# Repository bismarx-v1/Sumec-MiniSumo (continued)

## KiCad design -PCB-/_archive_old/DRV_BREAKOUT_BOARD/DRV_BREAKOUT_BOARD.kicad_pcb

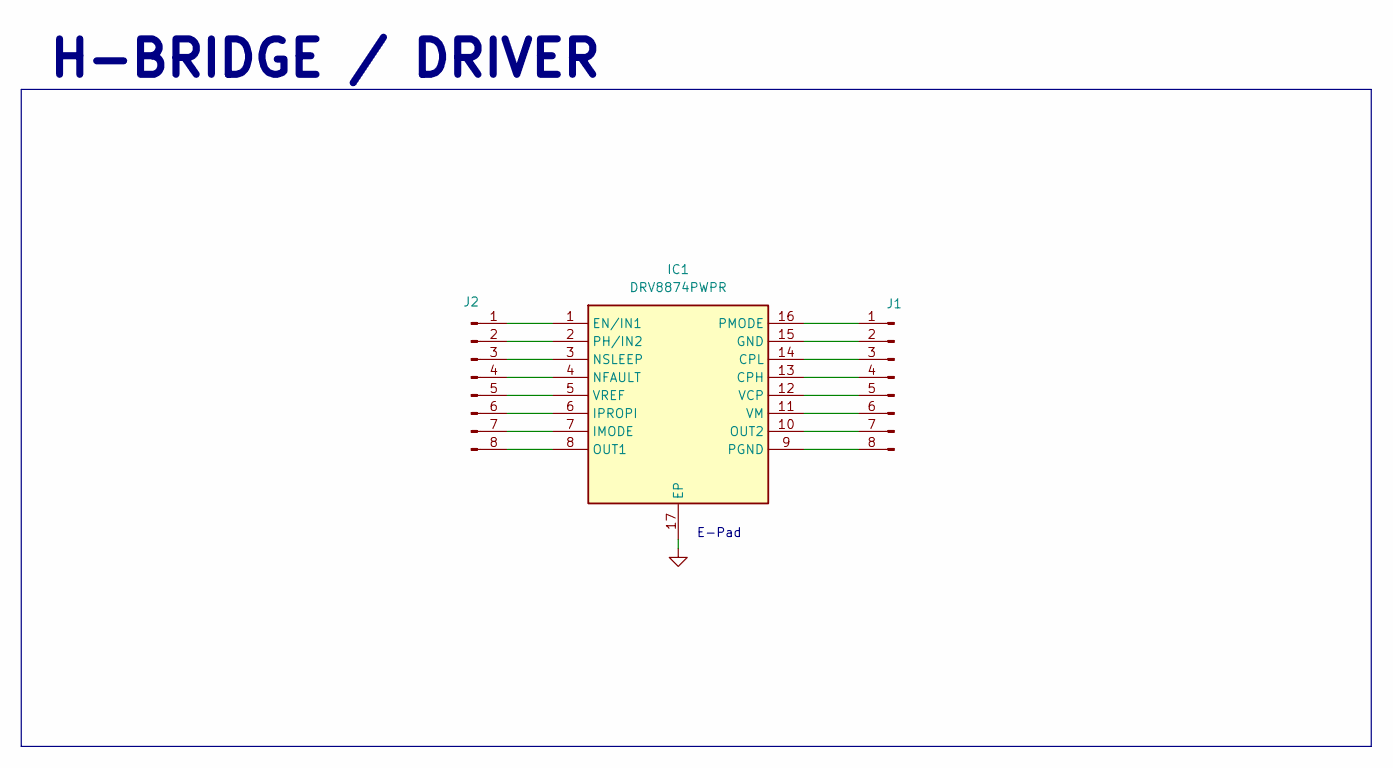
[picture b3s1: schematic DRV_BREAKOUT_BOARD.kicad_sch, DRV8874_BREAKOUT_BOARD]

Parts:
IC1: DRV8874PWPR; DRV8874; Manufacturer_Part_Number DRV8874PWPR; Mouser Part Number 595-DRV8874PWPR
J1, J2: Conn_01x08_Pin; PinHeader_1x08_P2.54mm_Vertical

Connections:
GND: IC1.17 (EP)
unnamed: IC1.13 (CPH), J1.4
unnamed: IC1.14 (CPL), J1.3
unnamed: IC1.1 (EN/IN1), J2.1
unnamed: IC1.15 (GND), J1.2
unnamed: IC1.7 (IMODE), J2.7
unnamed: IC1.6 (IPROPI), J2.6
unnamed: IC1.4 (NFAULT), J2.4
unnamed: IC1.3 (NSLEEP), J2.3
unnamed: IC1.8 (OUT1), J2.8
unnamed: IC1.10 (OUT2), J1.7
unnamed: IC1.9 (PGND), J1.8
unnamed: IC1.2 (PH/IN2), J2.2
unnamed: IC1.16 (PMODE), J1.1
unnamed: IC1.12 (VCP), J1.5
unnamed: IC1.11 (VM), J1.6
unnamed: IC1.5 (VREF), J2.5

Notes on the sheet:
H-BRIDGE / DRIVER
E-Pad

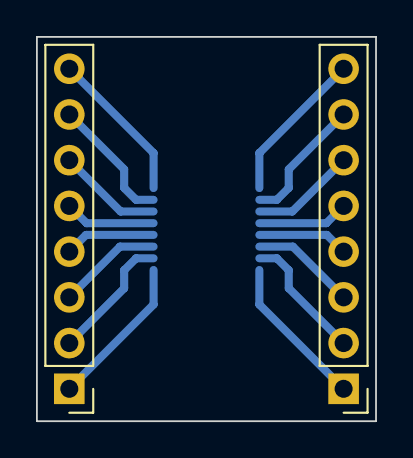
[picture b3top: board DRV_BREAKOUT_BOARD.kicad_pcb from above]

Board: 2 copper layers, 18.8 x 21.3 mm, 3 parts (1 on the bottom side), 16 nets.

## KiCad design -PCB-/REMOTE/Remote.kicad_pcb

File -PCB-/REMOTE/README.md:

Original project repository: https://github.com/p1rse/robot-sumo-start-module

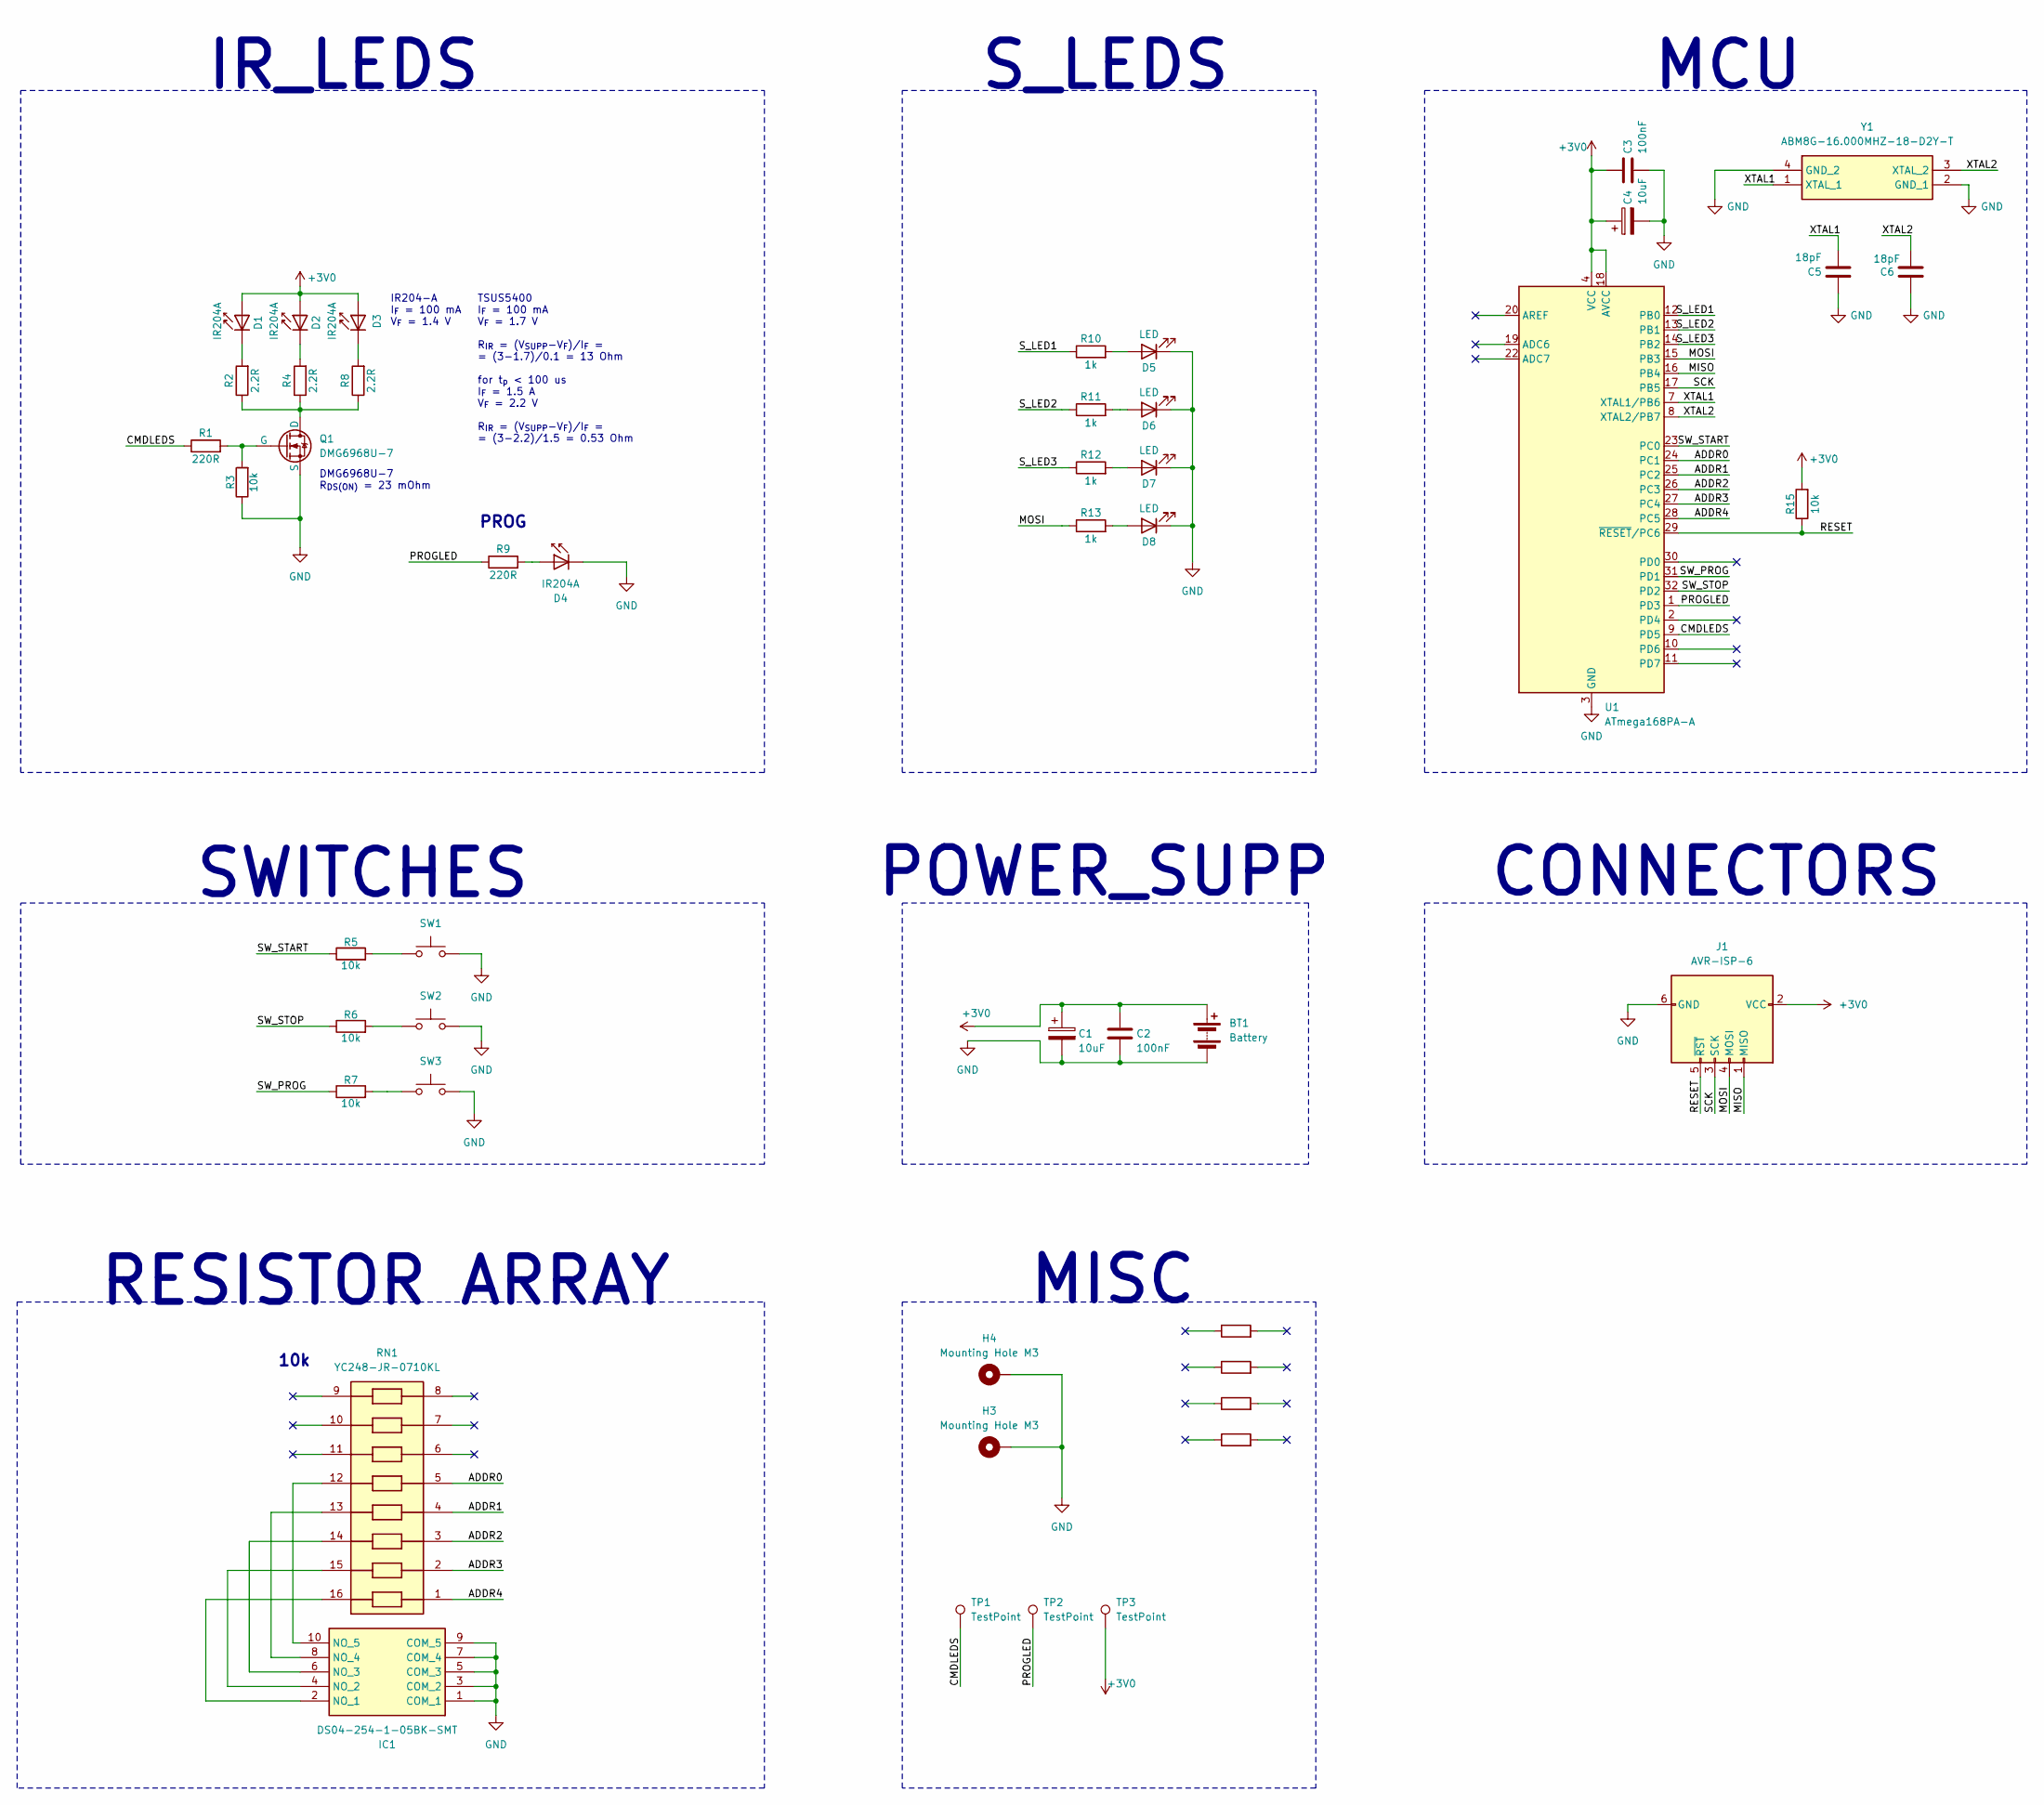
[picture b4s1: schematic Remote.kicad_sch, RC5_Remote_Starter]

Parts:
BT1: Battery; BatteryHolder_Keystone_2462_2xAA - no holes
C1, C4: 10uF; CP_EIA-3216-18_Kemet-A_Pad1.58x1.35mm_HandSolder
C2, C3: 100nF; C_0805_2012Metric_Pad1.18x1.45mm_HandSolder
C5, C6: 18pF; C_0805_2012Metric_Pad1.18x1.45mm_HandSolder
D1, D3: IR204A; LED_D3.0mm_Horizontal_O3.81mm_Z10.0mm_no_silk
D2: IR204A; LED_D3.0mm_Horizontal_O3.81mm_Z10.0mm_flipped_no_silk
D4: IR204A; LED_D3.0mm_Horizontal_O3.81mm_Z10.0mm_flipped
D5, D6, D7, D8: LED; LED_0805_2012Metric_Pad1.15x1.40mm_HandSolder
H3, H4: Mounting Hole M3; MountingHole_3.2mm_M3_Pad_Via
IC1: DS04-254-1-05BK-SMT; dip_switch; Mouser Part Number 490-DS04254105BK-SMT
J1: AVR-ISP-6; PinHeader_2x03_P2.54mm_Vertical
Q1: DMG6968U-7; SOT-23-3
R1, R9: 220R; R_0805_2012Metric_Pad1.20x1.40mm_HandSolder
R2, R4, R8: 2.2R; R_0805_2012Metric_Pad1.20x1.40mm_HandSolder
R3, R5, R6, R7, R15: 10k; R_0805_2012Metric_Pad1.20x1.40mm_HandSolder
R10, R11, R12, R13: 1k; R_0805_2012Metric_Pad1.20x1.40mm_HandSolder
R14: R; purosidenegative
R16: R; SPS LOGO
R17: R; boi
R18: R; Logo
RN1: YC248-JR-0710KL; resistor_array; Mouser Part Number 603-YC248-JR-0710KL
SW1, SW2, SW3: SW_Push; SW_PUSH_6mm
TP1, TP2, TP3: TestPoint; TestPoint_Pad_D1.5mm
U1: ATmega168PA-A; TQFP-32_7x7mm_P0.8mm
Y1: ABM8G-16.000MHZ-18-D2Y-T; crystal_smd; Mouser Part Number 815-ABM8G-16-18D2Y

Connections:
+3V0: BT1.1 (+), C1.1, C2.1, C3.1, C4.1, D1.2 (A), D2.2 (A), D3.2 (A), J1.2 (VCC), R15.2, TP3.1, U1.4 (VCC), U1.6 (VCC), U1.18 (AVCC)
/ADDR0: RN1.5, U1.24 (PC1)
/ADDR1: RN1.4, U1.25 (PC2)
/ADDR2: RN1.3, U1.26 (PC3)
/ADDR3: RN1.2, U1.27 (PC4)
/ADDR4: RN1.1, U1.28 (PC5)
/CMDLEDS: R1.1, TP1.1, U1.9 (PD5)
/MISO: J1.1 (MISO), U1.16 (PB4)
/MOSI: J1.4 (MOSI), R13.1, U1.15 (PB3)
/PROGLED: R9.1, TP2.1, U1.1 (PD3)
/RESET: J1.5 (~RST), R15.1, U1.29 (~RESET/PC6)
/SCK: J1.3 (SCK), U1.17 (PB5)
/SW_PROG: R7.1, U1.31 (PD1)
/SW_START: R5.1, U1.23 (PC0)
/SW_STOP: R6.1, U1.32 (PD2)
/S_LED1: R10.1, U1.12 (PB0)
/S_LED2: R11.1, U1.13 (PB1)
/S_LED3: R12.1, U1.14 (PB2)
/XTAL1: C5.2, U1.7 (XTAL1/PB6), Y1.1 (XTAL_1)
/XTAL2: C6.2, U1.8 (XTAL2/PB7), Y1.3 (XTAL_2)
GND: BT1.2 (-), C1.2, C2.2, C3.2, C4.2, C5.1, C6.1, D4.1 (K), D5.1 (K), D6.1 (K), D7.1 (K), D8.1 (K), H3.1, H4.1, IC1.1 (COM_1), IC1.3 (COM_2), IC1.5 (COM_3), IC1.7 (COM_4), IC1.9 (COM_5), J1.6 (GND), Q1.3 (S), R3.1, SW1.2, SW2.2, SW3.2, U1.3 (GND), U1.5 (GND), U1.21 (GND), Y1.2 (GND_1), Y1.4 (GND_2)
unnamed: D1.1 (K), R2.2
unnamed: D2.1 (K), R4.2
unnamed: D3.1 (K), R8.2
unnamed: D4.2 (A), R9.2
unnamed: D5.2 (A), R10.2
unnamed: D6.2 (A), R11.2
unnamed: D7.2 (A), R12.2
unnamed: D8.2 (A), R13.2
unnamed: IC1.2 (NO_1), RN1.16
unnamed: IC1.4 (NO_2), RN1.15
unnamed: IC1.6 (NO_3), RN1.14
unnamed: IC1.8 (NO_4), RN1.13
unnamed: IC1.10 (NO_5), RN1.12
unnamed: Q1.1 (D), R2.1, R4.1, R8.1
unnamed: Q1.2 (G), R1.2, R3.2
unnamed: R5.2, SW1.1
unnamed: R6.2, SW2.1
unnamed: R7.2, SW3.1

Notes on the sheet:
MISC
MCU
IR204-A I_{F} = 100 mA V_{F} = 1.4 V
SWITCHES
10k
POWER_SUPP
RESISTOR ARRAY
TSUS5400 I_{F} = 100 mA V_{F} = 1.7 V R_{IR} = (V_{SUPP}-V_{F})/I_{F} = = (3-1.7)/0.1 = 13 Ohm for t_{p} < 100 us I_{F} = 1.5 A V_{F} = 2.2 V R_{IR} = (V_{SUPP}-V_{F})/I_{F} = = (3-2.2)/1.5 = 0.53 Ohm
S_LEDS
CONNECTORS
IR_LEDS
PROG
DMG6968U-7 R_{DS(ON)} = 23 mOhm

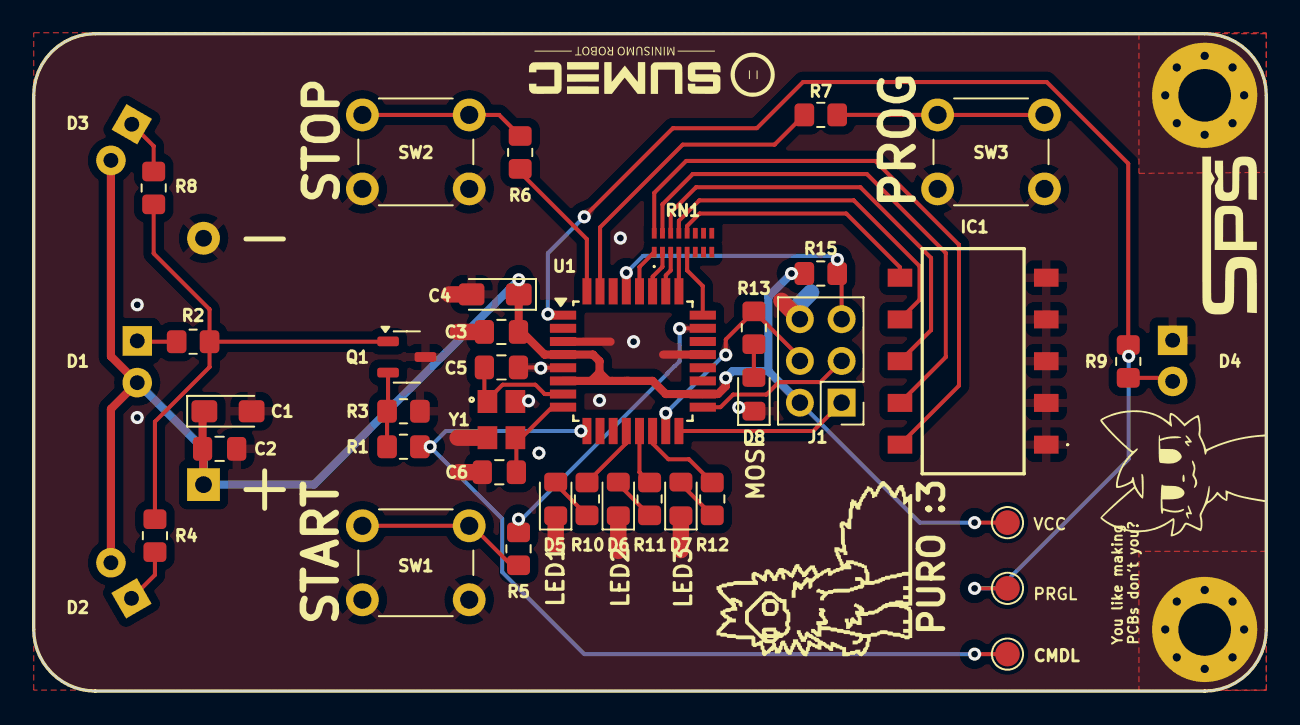
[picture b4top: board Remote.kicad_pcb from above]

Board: 2 copper layers, 75.0 x 40.0 mm, 47 parts (1 on the bottom side), 39 nets.

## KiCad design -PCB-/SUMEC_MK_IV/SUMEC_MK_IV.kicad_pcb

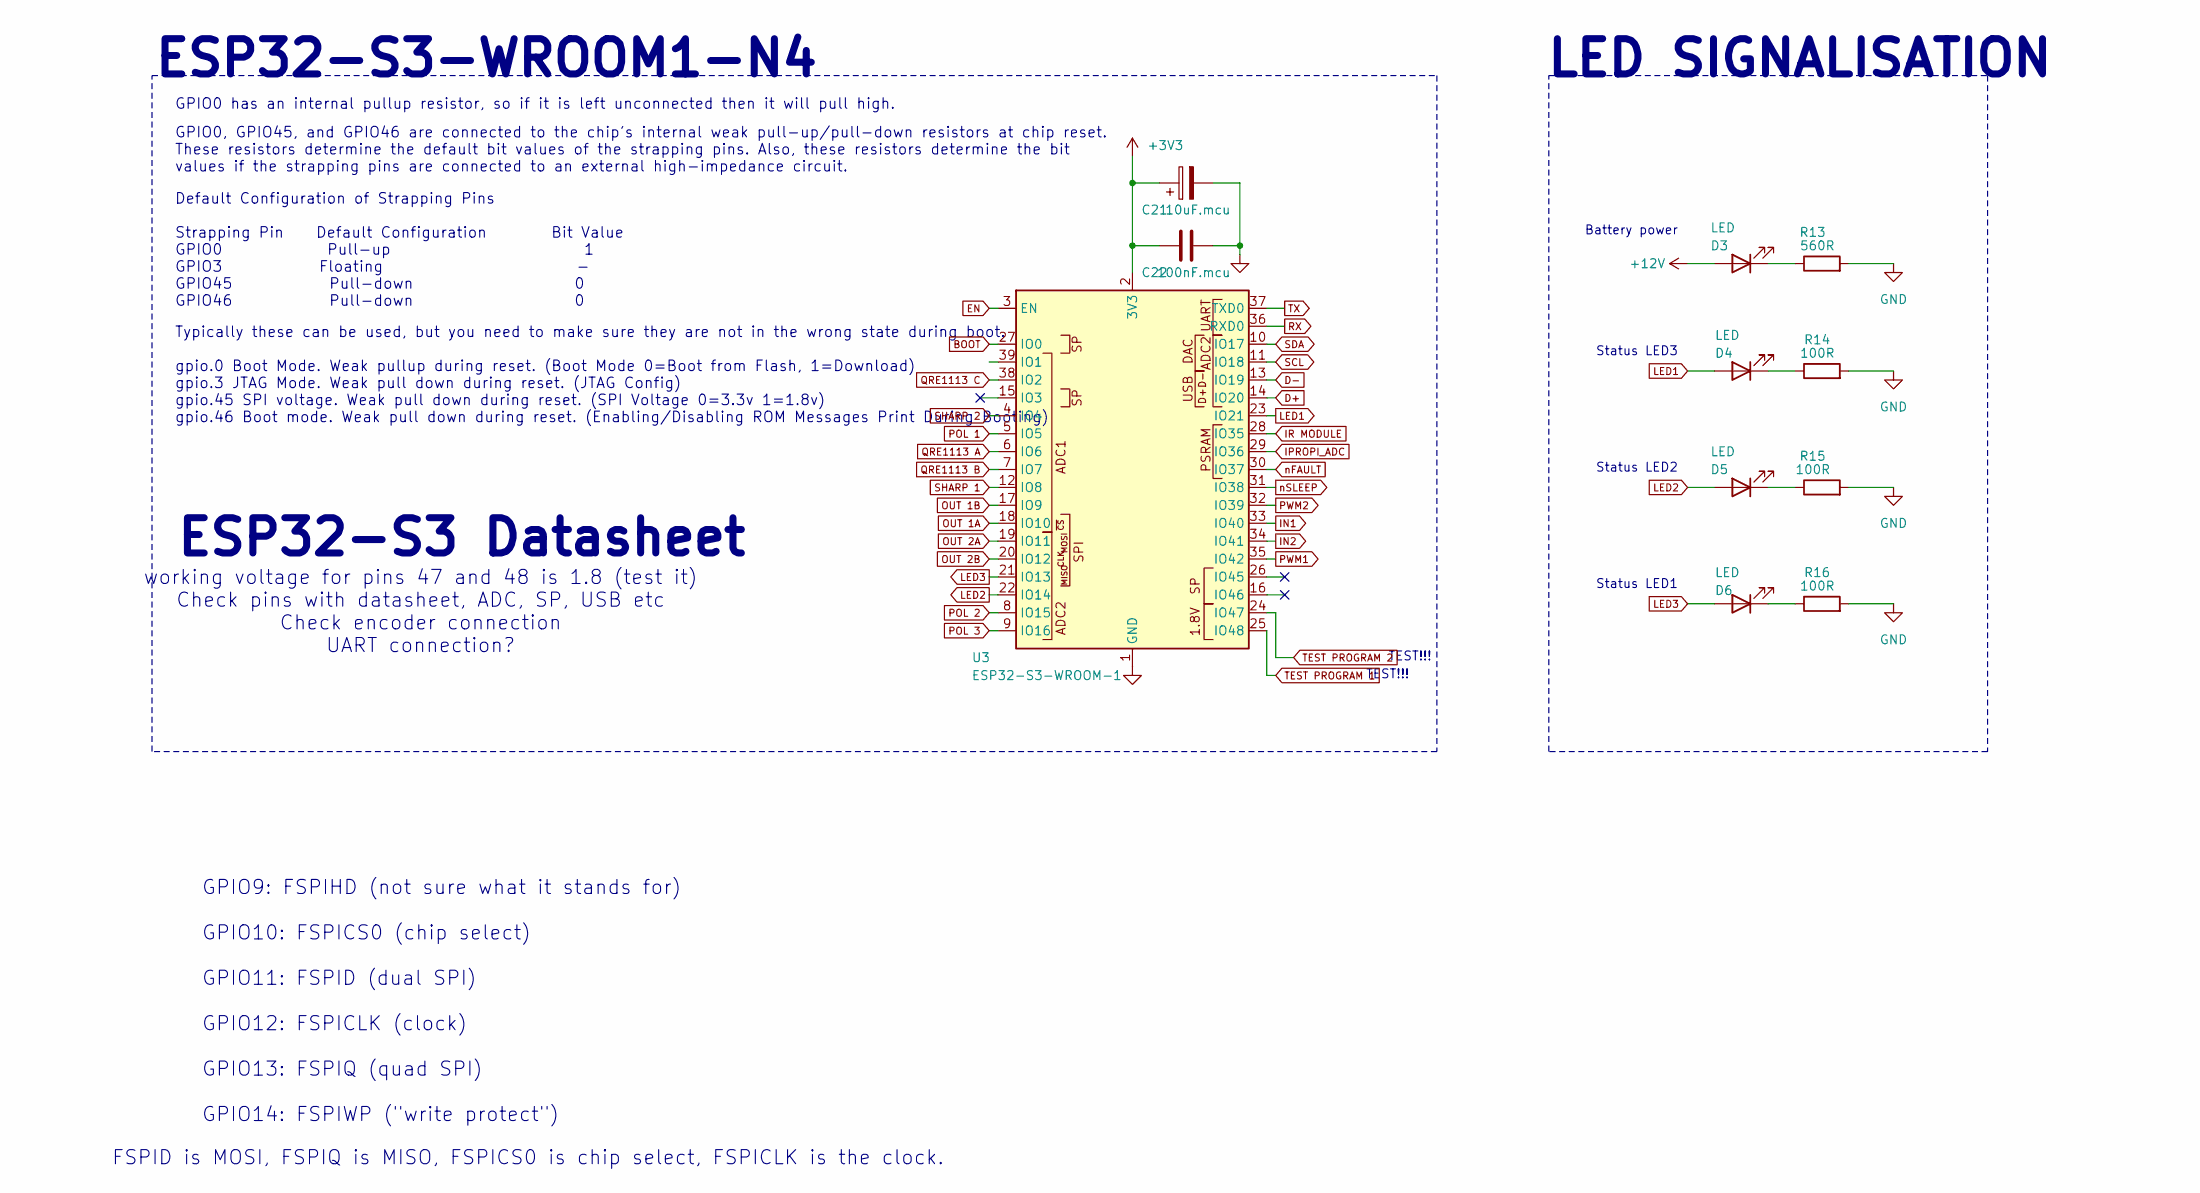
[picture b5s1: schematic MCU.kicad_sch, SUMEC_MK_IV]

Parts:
C21: 10uF.mcu; CP_EIA-3216-18_Kemet-A_Pad1.58x1.35mm_HandSolder
C22: 100nF.mcu; C_0805_2012Metric_Pad1.18x1.45mm_HandSolder
D3, D4, D5, D6: LED; LED_0805_2012Metric_Pad1.15x1.40mm_HandSolder
R13: 560R; R_0805_2012Metric_Pad1.20x1.40mm_HandSolder
R14, R15, R16: 100R; R_0805_2012Metric_Pad1.20x1.40mm_HandSolder
U3: ESP32-S3-WROOM-1

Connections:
+3V3: C21.1, C22.1, U3.2 (3V3); also elsewhere on the board
+12V: D3.2 (A); also elsewhere on the board
BOOT: U3.27 (IO0); also elsewhere on the board
D+: U3.14 (IO20); also elsewhere on the board
D-: U3.13 (IO19); also elsewhere on the board
EN: U3.3 (EN); also elsewhere on the board
GND: C21.2, C22.2, R13.2, R14.2, R15.2, R16.2, U3.1 (GND), U3.40 (GND), U3.41 (GND); also elsewhere on the board
IN1: U3.33 (IO40); also elsewhere on the board
IN2: U3.34 (IO41); also elsewhere on the board
IPROPI_ADC: U3.29 (IO36); also elsewhere on the board
IR MODULE: U3.28 (IO35); also elsewhere on the board
LED1: D4.2 (A), U3.23 (IO21)
LED2: D5.2 (A), U3.22 (IO14)
LED3: D6.2 (A), U3.21 (IO13)
unnamed: D3.1 (K), R13.1
unnamed: D4.1 (K), R14.1
unnamed: D5.1 (K), R15.1
unnamed: D6.1 (K), R16.1
OUT 1A: U3.18 (IO10); also elsewhere on the board
OUT 1B: U3.17 (IO9); also elsewhere on the board
OUT 2A: U3.19 (IO11); also elsewhere on the board
OUT 2B: U3.20 (IO12); also elsewhere on the board
POL 1: U3.5 (IO5); also elsewhere on the board
POL 2: U3.8 (IO15); also elsewhere on the board
POL 3: U3.9 (IO16); also elsewhere on the board
PWM1: U3.35 (IO42); also elsewhere on the board
PWM2: U3.32 (IO39); also elsewhere on the board
QRE1113 A: U3.6 (IO6); also elsewhere on the board
QRE1113 B: U3.7 (IO7); also elsewhere on the board
QRE1113 C: U3.38 (IO2); also elsewhere on the board
RX: U3.36 (RXD0); also elsewhere on the board
SCL: U3.11 (IO18); also elsewhere on the board
SDA: U3.10 (IO17); also elsewhere on the board
SHARP 1: U3.12 (IO8); also elsewhere on the board
SHARP 2: U3.4 (IO4); also elsewhere on the board
TEST PROGRAM 1: U3.25 (IO48); also elsewhere on the board
TEST PROGRAM 2: U3.24 (IO47); also elsewhere on the board
TX: U3.37 (TXD0); also elsewhere on the board
nFAULT: U3.30 (IO37); also elsewhere on the board
nSLEEP: U3.31 (IO38); also elsewhere on the board

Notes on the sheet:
Battery power
Typically these can be used, but you need to make sure they are not in the wrong state during boot. gpio.0 Boot Mode. Weak pullup during reset. (Boot Mode 0=Boot from Flash, 1=Download) gpio.3 JTAG Mode. Weak pull down during reset. (JTAG Config) gpio.45 SPI voltage. Weak pull down during reset. (S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
Status LED3
GPIO0 has an internal pullup resistor, so if it is left unconnected then it will pull high.
working voltage for pins 47 and 48 is 1.8 (test it) Check pins with datasheet, ADC, SP, USB etc Check encoder connection UART connection?
GPIO9: FSPIHD (not sure what it stands for) GPIO10: FSPICS0 (chip select) GPIO11: FSPID (dual SPI) GPIO12: FSPICLK (clock) GPIO13: FSPIQ (quad SPI) GPIO14: FSPIWP ("write protect")
ESP32-S3-WROOM1-N4
TEST!!!
GPIO0, GPIO45, and GPIO46 are connected to the chip's internal weak pull-up/pull-down resistors at chip reset. These resistors determine the default bit values of the strapping pins. Also, these resistors determine the bit values if the strapping pins are connected to an external high-impedance cir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
LED SIGNALISATION
FSPID is MOSI, FSPIQ is MISO, FSPICS0 is chip select, FSPICLK is the clock.
Status LED2
ESP32-S3 Datasheet
Status LED1
Default Configuration of Strapping Pins Strapping Pin Default Configuration Bit Value GPIO0 Pull-up 1 GPIO3 Floating - GPIO45 Pull-down 0 GPIO46 Pull-down 0

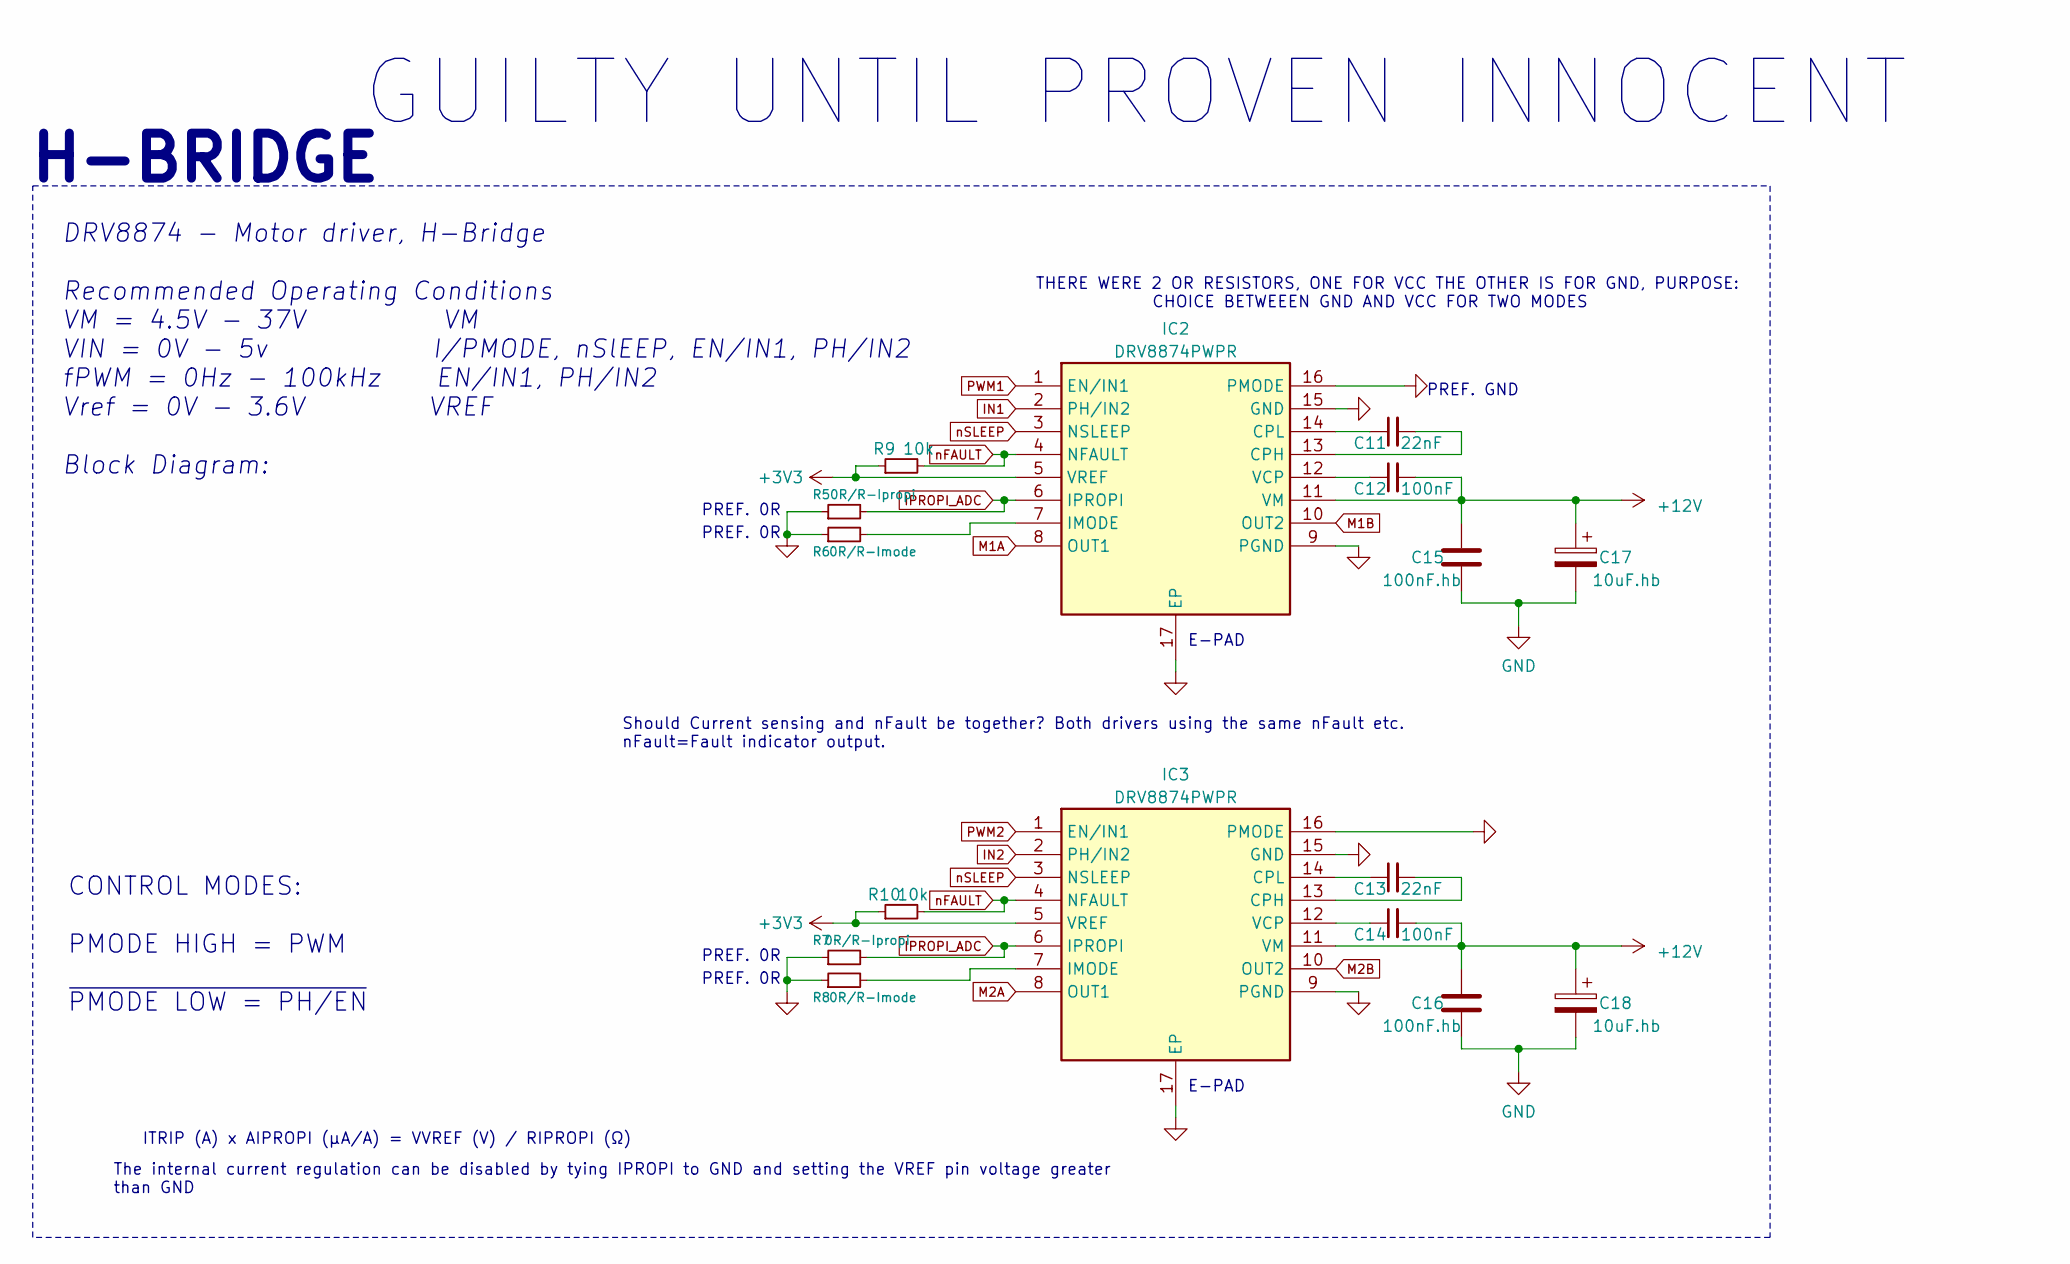
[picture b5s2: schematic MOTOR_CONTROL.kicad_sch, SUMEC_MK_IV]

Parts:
C11, C13: 22nF; C_0805_2012Metric_Pad1.18x1.45mm_HandSolder
C12, C14: 100nF; C_0805_2012Metric_Pad1.18x1.45mm_HandSolder
C15, C16: 100nF.hb; C_0805_2012Metric_Pad1.18x1.45mm_HandSolder
C17, C18: 10uF.hb; CP_EIA-3216-18_Kemet-A_Pad1.58x1.35mm_HandSolder
IC2, IC3: DRV8874PWPR; DRV8874; Manufacturer_Part_Number DRV8874PWPR; Mouser Part Number 595-DRV8874PWPR
R5, R7: 0R/R-Ipropi; R_0805_2012Metric_Pad1.20x1.40mm_HandSolder
R6, R8: 0R/R-Imode; R_0805_2012Metric_Pad1.20x1.40mm_HandSolder
R9, R10: 10k; R_0805_2012Metric_Pad1.20x1.40mm_HandSolder

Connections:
+3V3: IC2.5 (VREF), IC3.5 (VREF), R9.1, R10.1; also elsewhere on the board
+12V: C12.2, C14.2, C15.2, C16.2, C17.1, C18.1, IC2.11 (VM), IC3.11 (VM); also elsewhere on the board
GND: C15.1, C16.1, C17.2, C18.2, IC2.9 (PGND), IC2.15 (GND), IC2.16 (PMODE), IC2.17 (EP), IC3.9 (PGND), IC3.15 (GND), IC3.16 (PMODE), IC3.17 (EP), R5.1, R6.1, R7.1, R8.1; also elsewhere on the board
IN1: IC2.2 (PH/IN2); also elsewhere on the board
IN2: IC3.2 (PH/IN2); also elsewhere on the board
IPROPI_ADC: IC2.6 (IPROPI), IC3.6 (IPROPI), R5.2, R7.2; also elsewhere on the board
M1A: IC2.8 (OUT1); also elsewhere on the board
M1B: IC2.10 (OUT2); also elsewhere on the board
M2A: IC3.8 (OUT1); also elsewhere on the board
M2B: IC3.10 (OUT2); also elsewhere on the board
unnamed: C11.2, IC2.13 (CPH)
unnamed: C11.1, IC2.14 (CPL)
unnamed: IC2.7 (IMODE), R6.2
unnamed: C12.1, IC2.12 (VCP)
unnamed: C13.2, IC3.13 (CPH)
unnamed: C13.1, IC3.14 (CPL)
unnamed: IC3.7 (IMODE), R8.2
unnamed: C14.1, IC3.12 (VCP)
PWM1: IC2.1 (EN/IN1); also elsewhere on the board
PWM2: IC3.1 (EN/IN1); also elsewhere on the board
nFAULT: IC2.4 (NFAULT), IC3.4 (NFAULT), R9.2, R10.2; also elsewhere on the board
nSLEEP: IC2.3 (NSLEEP), IC3.3 (NSLEEP); also elsewhere on the board

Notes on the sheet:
PREF. 0R
CONTROL MODES: PMODE HIGH = PWM ~{PMODE LOW = PH/EN}
PREF. GND
E-PAD
The internal current regulation can be disabled by tying IPROPI to GND and setting the VREF pin voltage greater than GND
DRV8874 - Motor driver, H-Bridge Recommended Operating Conditions VM = 4.5V - 37V VM VIN = 0V - 5v I/PMODE, nSlEEP, EN/IN1, PH/IN2 fPWM = 0Hz - 100kHz EN/IN1, PH/IN2 Vref = 0V - 3.6V VREF Block Diagram:
ITRIP (A) x AIPROPI (μA/A) = VVREF (V) / RIPROPI (Ω)
THERE WERE 2 OR RESISTORS, ONE FOR VCC THE OTHER IS FOR GND, PURPOSE: CHOICE BETWEEEN GND AND VCC FOR TWO MODES
Should Current sensing and nFault be together? Both drivers using the same nFault etc. nFault=Fault indicator output.
H-BRIDGE
GUILTY UNTIL PROVEN INNOCENT

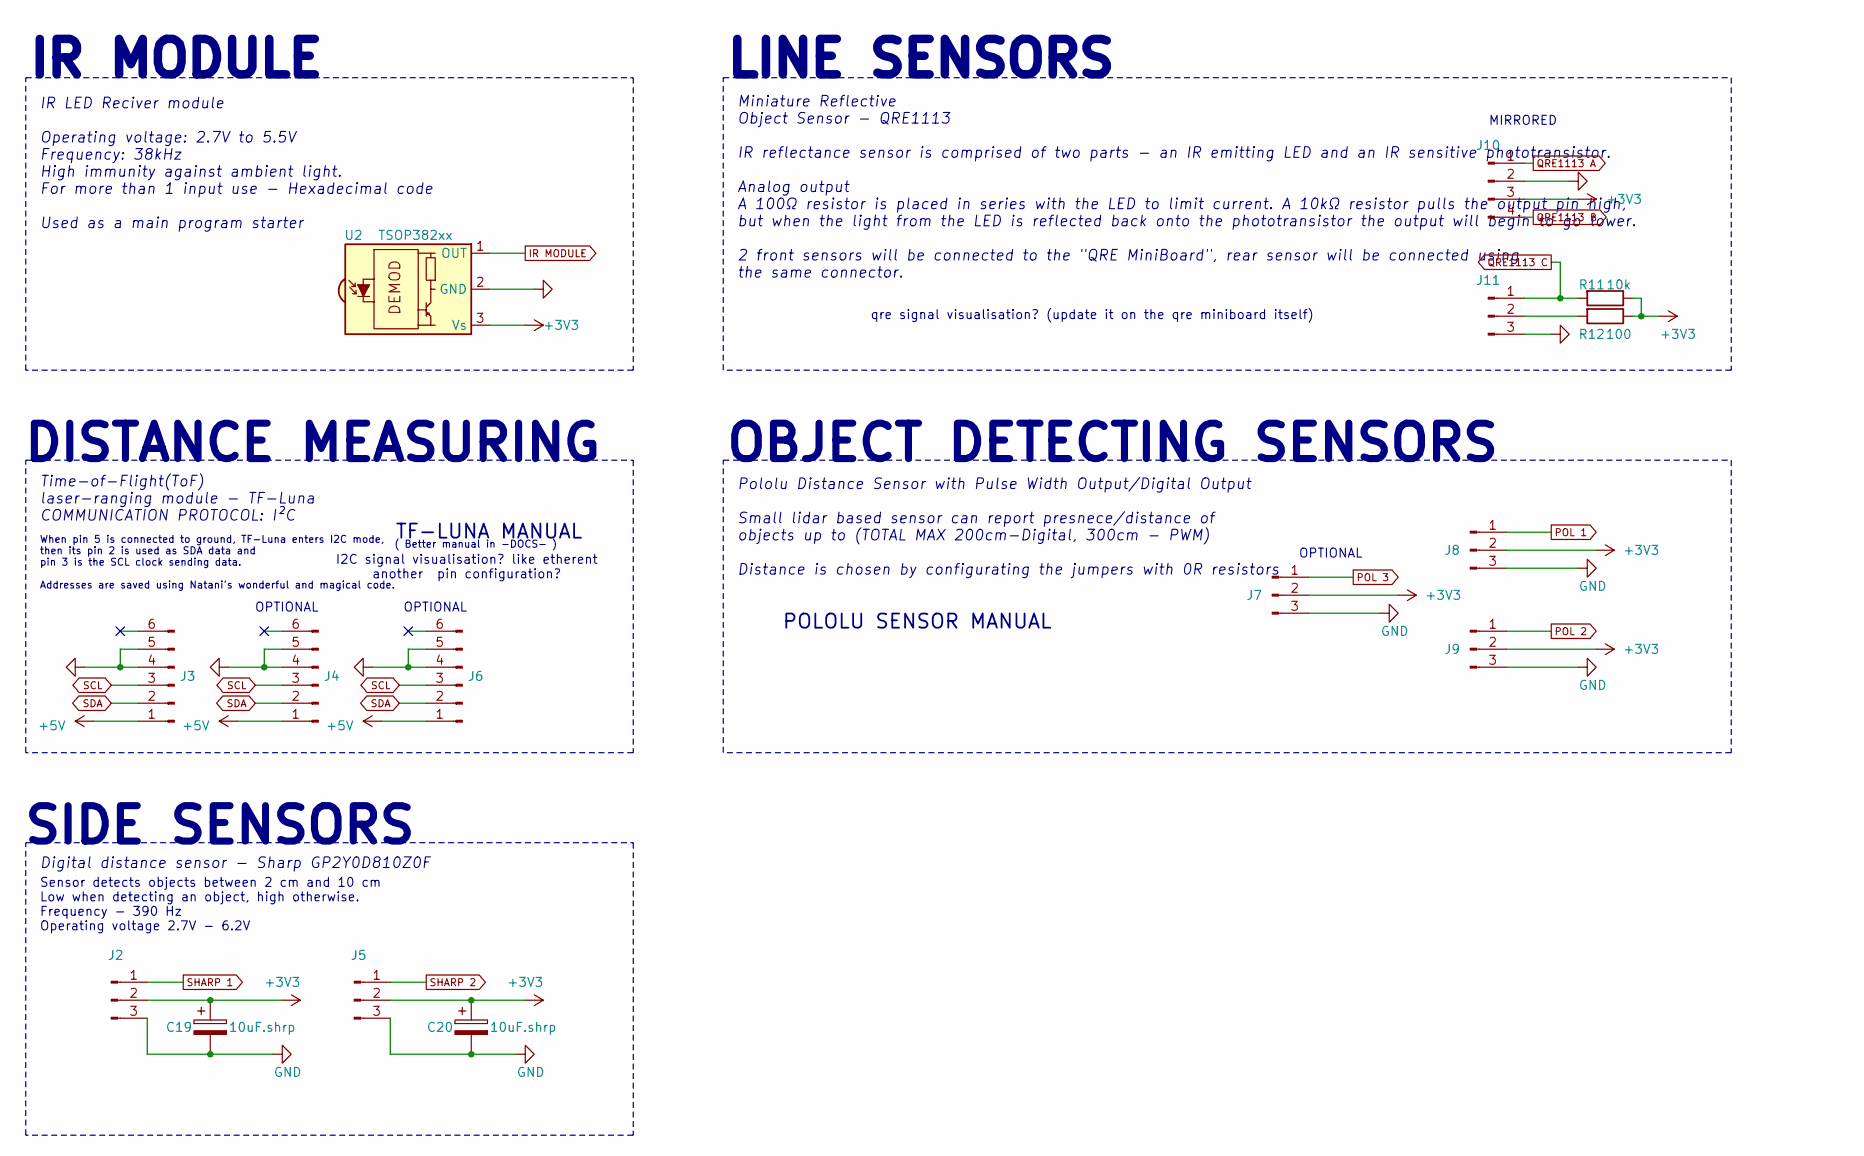
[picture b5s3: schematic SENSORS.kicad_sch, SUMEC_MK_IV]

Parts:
C19, C20: 10uF.shrp; CP_EIA-3216-18_Kemet-A_Pad1.58x1.35mm_HandSolder
J2, J5, J7, J8, J9, J11: Conn_01x03_Pin; Molex_PicoBlade_53398-0371_1x03-1MP_P1.25mm_Vertical
J3, J4, J6: Conn_01x06_Pin; Molex_PicoBlade_53398-0671_1x06-1MP_P1.25mm_Vertical
J10: Conn_01x04_Pin; Molex_PicoBlade_53398-0471_1x04-1MP_P1.25mm_Vertical
R11: 10k; R_0805_2012Metric_Pad1.20x1.40mm_HandSolder
R12: 100; R_0805_2012Metric_Pad1.20x1.40mm_HandSolder
U2: TSOP382xx; TSOP

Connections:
+3V3: C19.1, C20.1, J2.2, J5.2, J7.2, J8.2, J9.2, J10.3, R11.1, R12.1, U2.3 (Vs); also elsewhere on the board
+5V: J3.1, J4.1, J6.1; also elsewhere on the board
GND: C19.2, C20.2, J2.3, J3.4, J3.5, J4.4, J4.5, J5.3, J6.4, J6.5, J7.3, J8.3, J9.3, J10.2, J11.3, U2.2 (GND); also elsewhere on the board
IR MODULE: U2.1 (OUT); also elsewhere on the board
unnamed: J11.2, R12.2
POL 1: J8.1; also elsewhere on the board
POL 2: J9.1; also elsewhere on the board
POL 3: J7.1; also elsewhere on the board
QRE1113 A: J10.1; also elsewhere on the board
QRE1113 B: J10.4; also elsewhere on the board
QRE1113 C: J11.1, R11.2; also elsewhere on the board
SCL: J3.3, J4.3, J6.3; also elsewhere on the board
SDA: J3.2, J4.2, J6.2; also elsewhere on the board
SHARP 1: J2.1; also elsewhere on the board
SHARP 2: J5.1; also elsewhere on the board

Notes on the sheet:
Sensor detects objects between 2 cm and 10 cm Low when detecting an object, high otherwise. Frequency - 390 Hz Operating voltage 2.7V - 6.2V
OPTIONAL
When pin 5 is connected to ground, TF-Luna enters I2C mode, then its pin 2 is used as SDA data and pin 3 is the SCL clock sending data. Addresses are saved using Natani's wonderful and magical code.
qre signal visualisation? (update it on the qre miniboard itself)
TF-LUNA MANUAL
IR LED Reciver module Operating voltage: 2.7V to 5.5V Frequency: 38kHz High immunity against ambient light. For more than 1 input use - Hexadecimal code Used as a main program starter
IR MODULE
Digital distance sensor - Sharp GP2Y0D810Z0F
LINE SENSORS
Miniature Reflective Object Sensor - QRE1113 IR reflectance sensor is comprised of two parts - an IR emitting LED and an IR sensitive phototransistor. Analog output A 100Ω resistor is placed in series with the LED to limit current. A 10kΩ resistor pulls the output pin high, but when the light from 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
OBJECT DETECTING SENSORS
Pololu Distance Sensor with Pulse Width Output/Digital Output Small lidar based sensor can report presnece/distance of objects up to (TOTAL MAX 200cm-Digital, 300cm - PWM) Distance is chosen by configurating the jumpers with 0R resistors
DISTANCE MEASURING
Time-of-Flight(ToF) laser-ranging module - TF-Luna COMMUNICATION PROTOCOL: I²C
( Better manual in -DOCS- )
SIDE SENSORS
I2C signal visualisation? like etherent another pin configuration?
POLOLU SENSOR MANUAL
MIRRORED
